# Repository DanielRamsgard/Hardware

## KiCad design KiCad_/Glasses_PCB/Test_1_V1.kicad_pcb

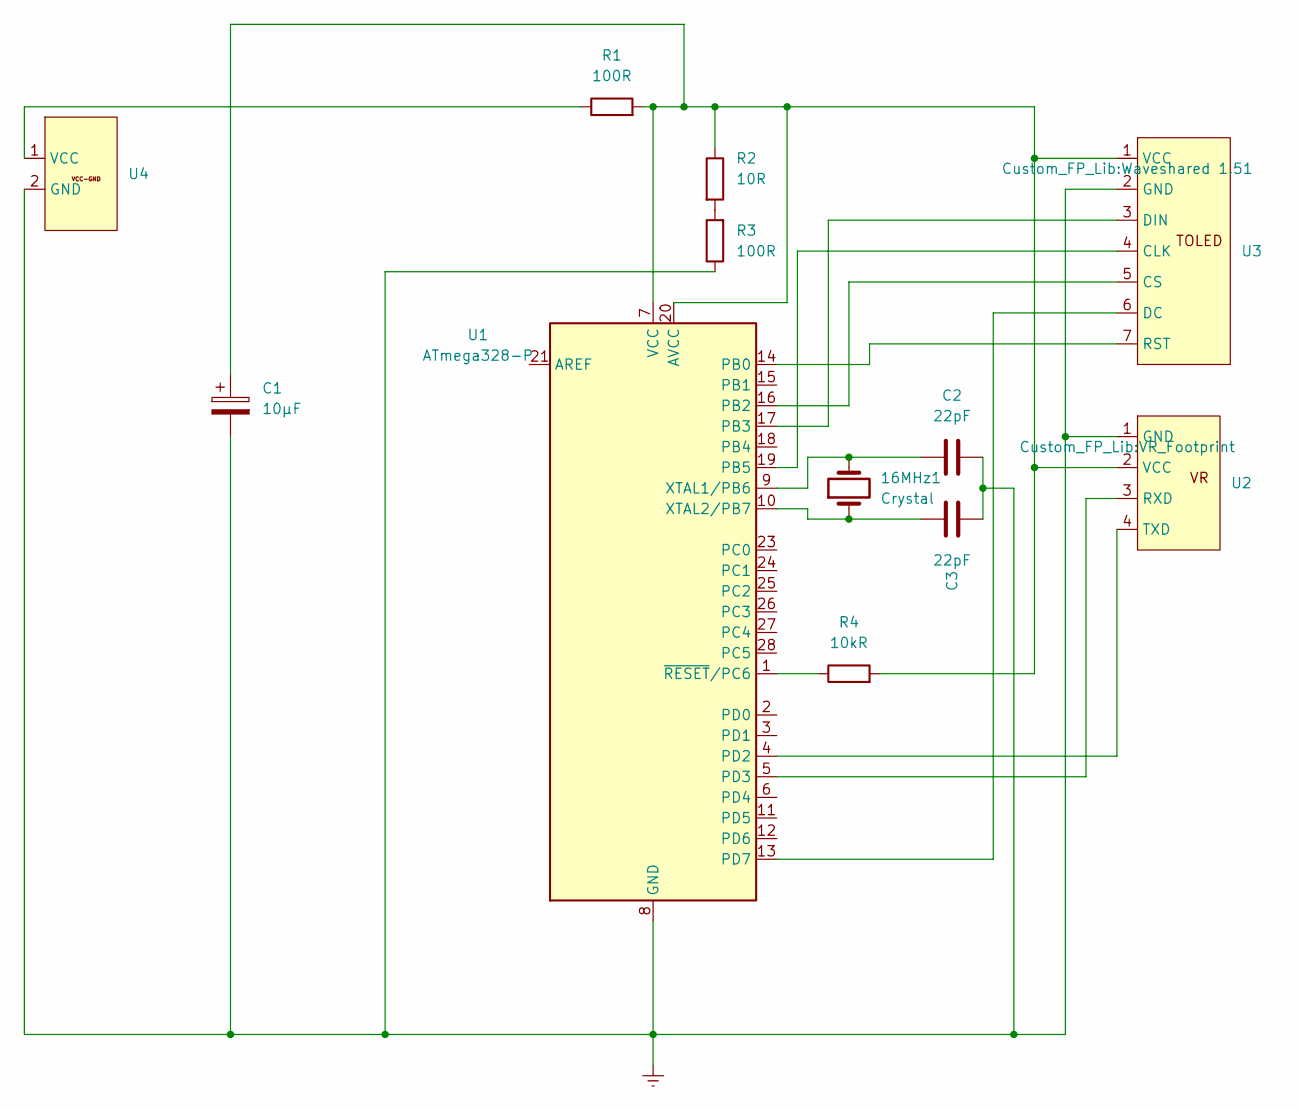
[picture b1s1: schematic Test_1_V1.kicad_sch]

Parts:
16MHz1: Crystal; Crystal_HC49-4H_Vertical
C1: 10µF; Through-Hole Cap
C2, C3: 22pF; Through-Hole Cap
R1, R3: 100R; Through-Hole Resistor
R2: 10R; Through-Hole Resistor
R4: 10kR; Through-Hole Resistor
U1: ATmega328-P; DIP-28_W7.62mm_Socket
U2: VR_Footprint
U3: Waveshared 1.51
U4: Power-Source

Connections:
Earth: C1.2, C2.2, C3.2, R3.1, U1.8 (GND), U1.22 (GND), U2.1 (GND), U3.2 (GND), U4.2 (GND)
unnamed: R2.2, R3.2
unnamed: C1.1, R1.2, R2.1, R4.2, U1.7 (VCC), U1.20 (AVCC), U2.2 (VCC), U3.1 (VCC)
unnamed: U1.14 (PB0), U3.7 (RST)
unnamed: U1.16 (PB2), U3.5 (CS)
unnamed: U1.17 (PB3), U3.3 (DIN)
unnamed: U1.19 (PB5), U3.4 (CLK)
unnamed: U1.4 (PD2), U2.4 (TXD)
unnamed: U1.5 (PD3), U2.3 (RXD)
unnamed: U1.13 (PD7), U3.6 (DC)
unnamed: 16MHz1.2, C2.1, U1.9 (XTAL1/PB6)
unnamed: 16MHz1.1, C3.1, U1.10 (XTAL2/PB7)
unnamed: R4.1, U1.1 (~RESET/PC6)
unnamed: R1.1, U4.1 (VCC)

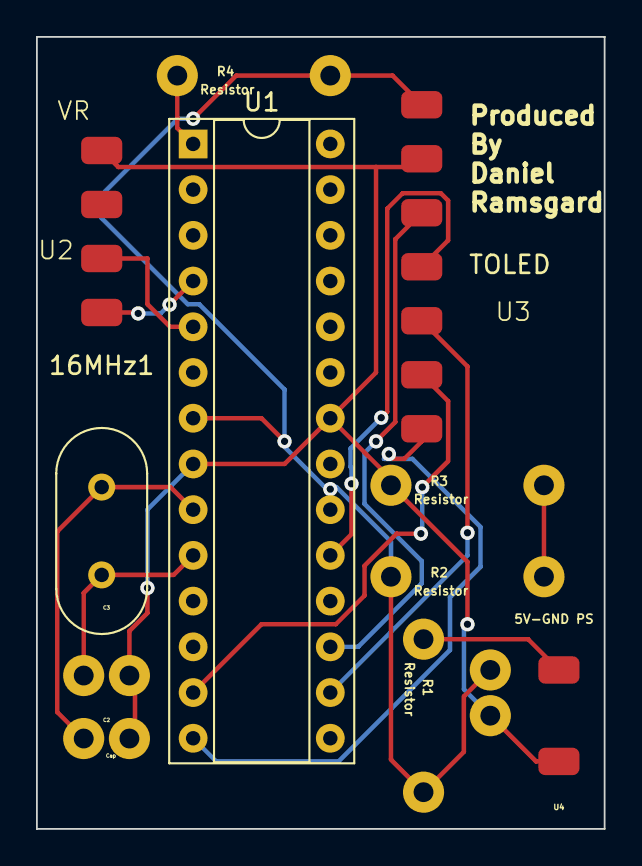
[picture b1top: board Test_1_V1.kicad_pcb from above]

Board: 2 copper layers, 31.5 x 44.0 mm, 12 parts (0 on the bottom side), 14 nets.

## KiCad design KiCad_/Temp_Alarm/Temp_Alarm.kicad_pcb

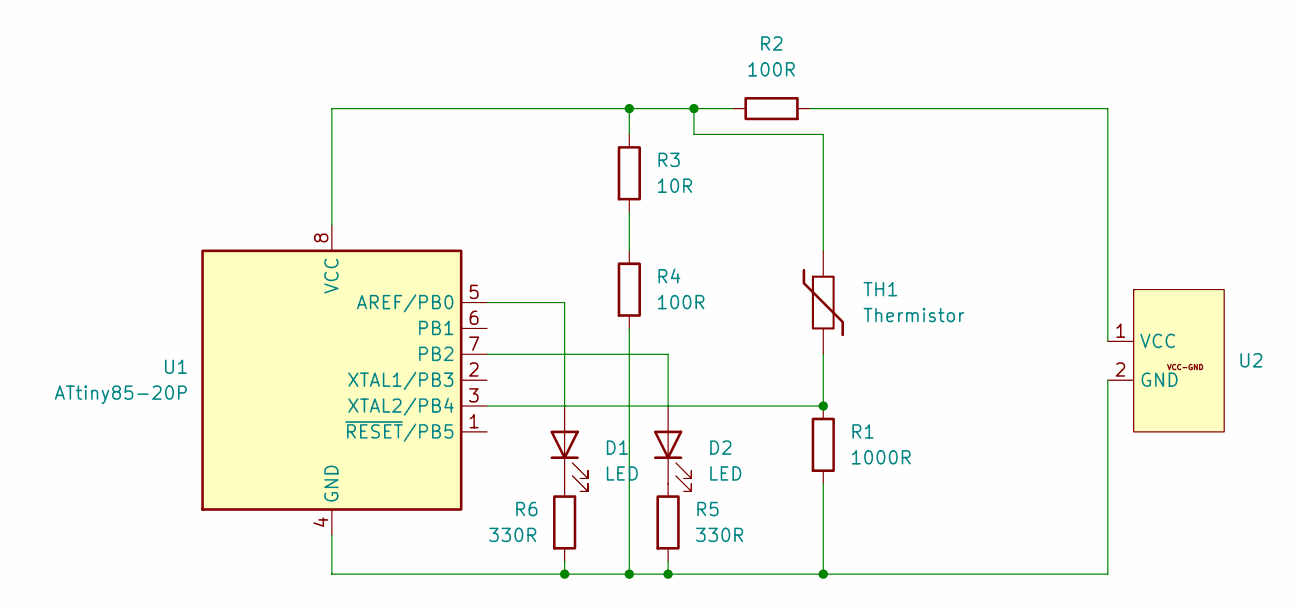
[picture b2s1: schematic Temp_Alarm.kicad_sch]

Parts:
D1, D2: LED; LED_D4.0mm
R1: 1000R; Through-Hole Resistor
R2, R4: 100R; Through-Hole Resistor
R3: 10R; Through-Hole Resistor
R5, R6: 330R; Through-Hole Resistor
TH1: Thermistor; Through-Hole Cap
U1: ATtiny85-20P; DIP-8_W7.62mm
U2: Power-Source

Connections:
unnamed: D1.2 (A), U1.5 (AREF/PB0)
unnamed: D1.1 (K), R6.1
unnamed: D2.2 (A), U1.7 (PB2)
unnamed: D2.1 (K), R5.1
unnamed: R3.2, R4.1
unnamed: R1.2, R4.2, R5.2, R6.2, U1.4 (GND), U2.2 (GND)
unnamed: R2.1, R3.1, TH1.1, U1.8 (VCC)
unnamed: R1.1, TH1.2, U1.3 (XTAL2/PB4)
unnamed: R2.2, U2.1 (VCC)

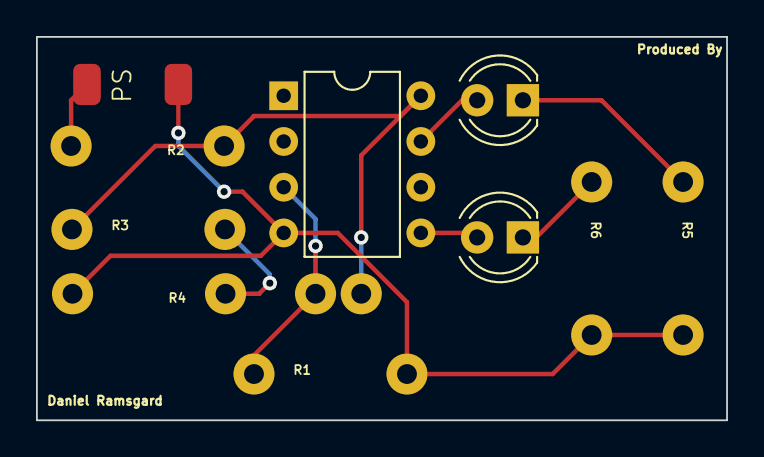
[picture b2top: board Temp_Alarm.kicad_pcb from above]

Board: 2 copper layers, 38.3 x 21.3 mm, 11 parts (0 on the bottom side), 9 nets.

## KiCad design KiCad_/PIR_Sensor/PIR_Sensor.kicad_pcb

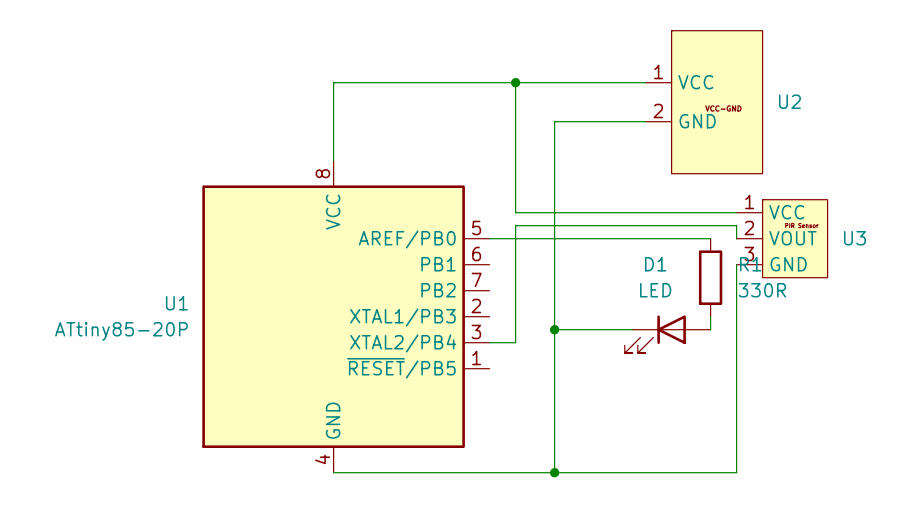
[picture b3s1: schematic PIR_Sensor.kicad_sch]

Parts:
D1: LED; LED_D4.0mm
R1: 330R; Through-Hole Resistor
U1: ATtiny85-20P; DIP-8_W7.62mm
U2: Power-Source
U3: PinHeader_1x03_P2.54mm_Vertical

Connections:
unnamed: D1.2 (A), R1.2
unnamed: D1.1 (K), U1.4 (GND), U2.2 (GND), U3.3 (GND)
unnamed: R1.1, U1.5 (AREF/PB0)
unnamed: U1.8 (VCC), U2.1 (VCC), U3.1 (VCC)
unnamed: U1.3 (XTAL2/PB4), U3.2 (VOUT)

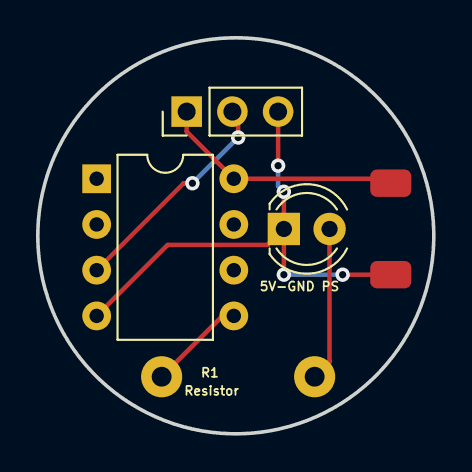
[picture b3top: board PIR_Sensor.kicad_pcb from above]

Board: 2 copper layers, 22.0 x 22.0 mm, 5 parts (0 on the bottom side), 5 nets.

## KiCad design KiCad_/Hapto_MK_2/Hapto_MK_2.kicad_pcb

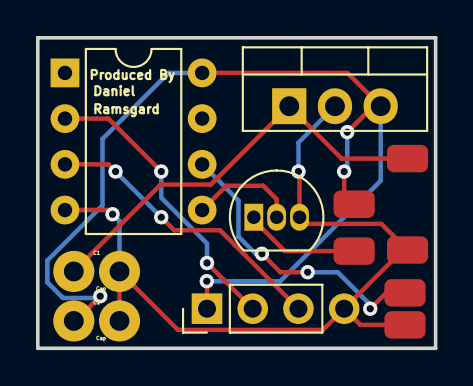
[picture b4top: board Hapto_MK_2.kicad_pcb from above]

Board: 2 copper layers, 22.1 x 17.2 mm, 9 parts (0 on the bottom side), 8 nets.

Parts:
C1, C2: C; Through-Hole Cap
Q1: BC337; TO-92_Inline
U1: Vibration_Motor
U2: ATtiny85-20P; DIP-8_W7.62mm
U3: LM7805_TO220; TO-220-3_Vertical
U4: Power-Source
U5: HC-SR04
U6: PB_No_Solder

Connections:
unnamed: Q1.2 (B), U2.5 (AREF/PB0)
unnamed: Q1.1 (C), U1.2 (GND)
unnamed: C1.2, C2.2, Q1.3 (E), U2.4 (GND), U3.2 (GND), U4.2 (GND), U5.4 (GND), U6.2 (GND)
unnamed: C2.1, U1.1 (VCC), U2.8 (VCC), U3.3 (VO), U5.1 (VCC)
unnamed: U2.6 (PB1), U6.1 (VCC)
unnamed: U2.2 (XTAL1/PB3), U5.2 (Trig)
unnamed: U2.3 (XTAL2/PB4), U5.3 (Echo)
unnamed: C1.1, U3.1 (VI), U4.1 (VCC)

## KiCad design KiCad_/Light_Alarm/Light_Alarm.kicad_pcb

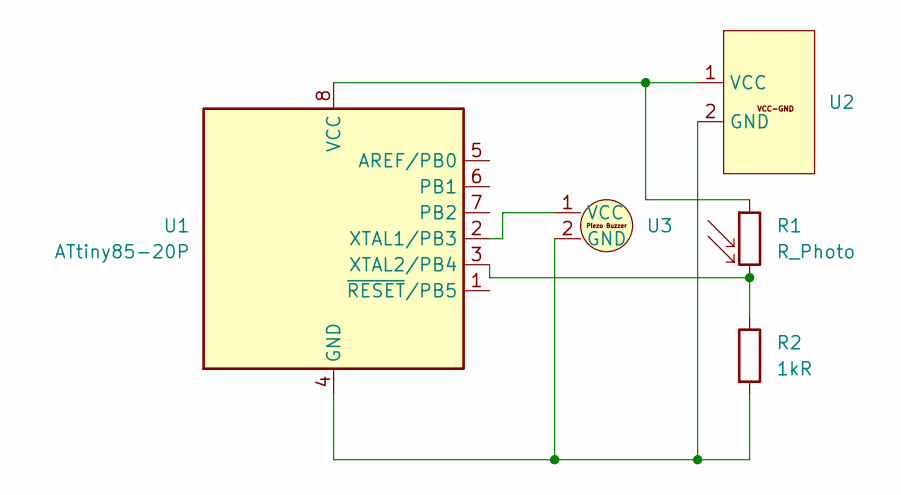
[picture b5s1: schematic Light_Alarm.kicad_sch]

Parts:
R1: R_Photo; Through-Hole Cap
R2: 1kR; Through-Hole Resistor
U1: ATtiny85-20P; DIP-8_W7.62mm
U2: Power-Source
U3: Piezo Buzzer

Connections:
unnamed: R2.2, U1.4 (GND), U2.2 (GND), U3.2 (GND)
unnamed: R1.1, U1.8 (VCC), U2.1 (VCC)
unnamed: U1.2 (XTAL1/PB3), U3.1 (VCC)
unnamed: R1.2, R2.1, U1.3 (XTAL2/PB4)

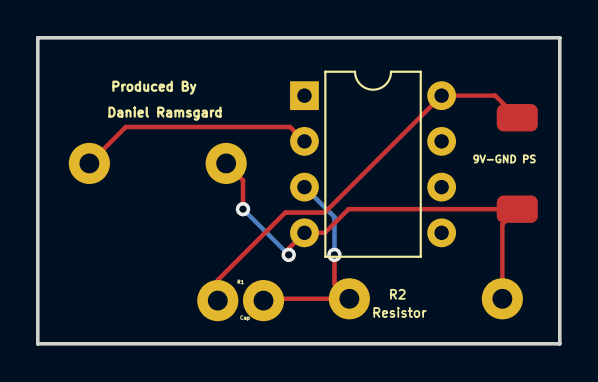
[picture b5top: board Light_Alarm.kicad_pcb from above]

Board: 2 copper layers, 29.0 x 17.0 mm, 5 parts (0 on the bottom side), 4 nets.

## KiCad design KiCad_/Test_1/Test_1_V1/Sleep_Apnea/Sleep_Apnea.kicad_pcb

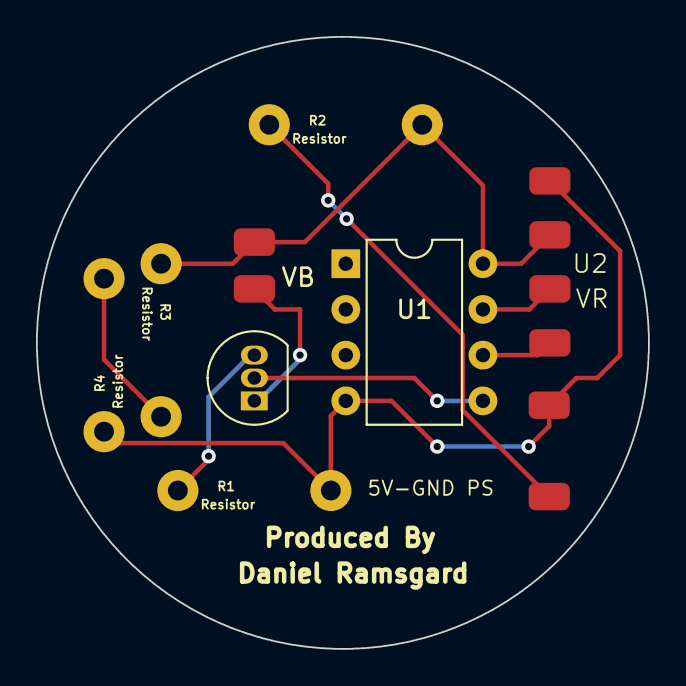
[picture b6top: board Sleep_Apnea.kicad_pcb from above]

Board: 2 copper layers, 34.0 x 34.0 mm, 9 parts (0 on the bottom side), 9 nets.

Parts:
Q1: BC337; TO-92_Inline
R1, R3: 10R; Through-Hole Resistor
R2, R4: 100R; Through-Hole Resistor
U1: ATtiny85-20P; DIP-8_W7.62mm
U2: VR_Footprint
U3: Vibration_Motor
U4: Power-Source

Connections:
unnamed: Q1.2 (B), U1.5 (AREF/PB0)
unnamed: Q1.1 (C), U3.2 (GND)
unnamed: Q1.3 (E), R1.1
unnamed: R3.2, R4.2
unnamed: R1.2, R4.1, U1.4 (GND), U2.1 (GND), U4.2 (GND)
unnamed: U1.6 (PB1), U2.4 (TXD)
unnamed: U1.7 (PB2), U2.3 (RXD)
unnamed: R2.2, R3.1, U1.8 (VCC), U2.2 (VCC), U3.1 (VCC)
unnamed: R2.1, U4.1 (VCC)
